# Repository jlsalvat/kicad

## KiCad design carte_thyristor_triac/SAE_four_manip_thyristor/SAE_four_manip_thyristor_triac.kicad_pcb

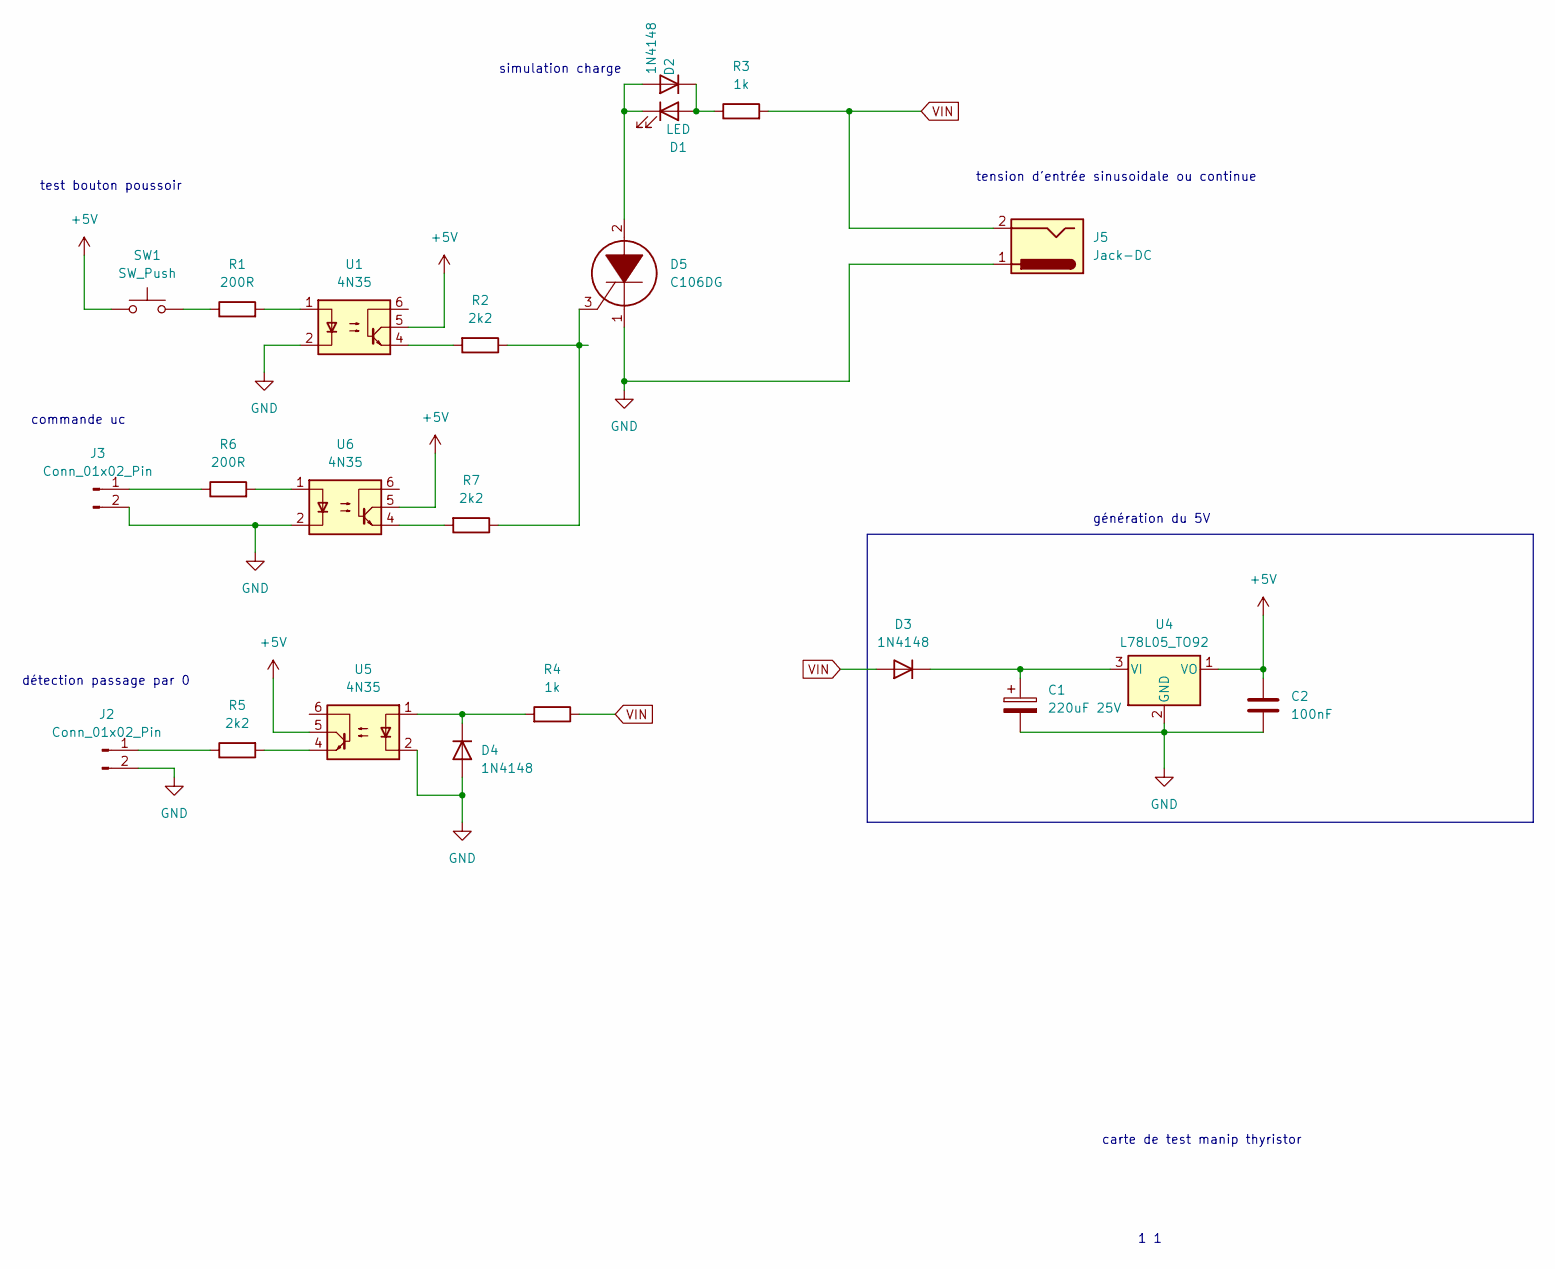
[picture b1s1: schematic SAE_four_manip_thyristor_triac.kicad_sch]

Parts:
C1: 220uF 25V; C_Radial_D6.3mm_H5.0mm_P2.50mm
C2: 100nF; C_Rect_L4.6mm_W3.0mm_P2.50mm_MKS02_FKP02
D1: LED; LED_D3.0mm
D2, D3, D4: 1N4148; D_DO-35_SOD27_P7.62mm_Horizontal
D5: C106DG; Manufacturer_Part_Number C106DG; Mouser Part Number 863-C106DG
J2, J3: Conn_01x02_Pin; PinHeader_1x02_P2.54mm_Vertical
J5: Jack-DC; BarrelJack_GCT_DCJ200-10-A_Horizontal_3D
R1, R6: 200R; R_Axial_DIN0207_L6.3mm_D2.5mm_P10.16mm_Horizontal
R2, R5, R7: 2k2; R_Axial_DIN0207_L6.3mm_D2.5mm_P10.16mm_Horizontal
R3, R4: 1k; R_Axial_DIN0207_L6.3mm_D2.5mm_P10.16mm_Horizontal
SW1: SW_Push; SW_PUSH_6mm
U1, U5, U6: 4N35; DIP-6_W7.62mm
U4: L78L05_TO92; TO-92_Inline

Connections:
+5V: C2.1, SW1.1, U1.5, U4.1 (VO), U5.5, U6.5
GND: C1.2, C2.2, D4.2 (A), D5.1, J2.2, J3.2, J5.1, U1.2, U4.2 (GND), U5.2, U6.2
unnamed: D1.2 (A), D2.1 (K), R3.1
unnamed: D1.1 (K), D2.2 (A), D5.2
unnamed: C1.1, D3.1 (K), U4.3 (VI)
unnamed: D4.1 (K), R4.2, U5.1
unnamed: D5.3, R2.1, R7.1
unnamed: J2.1, R5.1
unnamed: J3.1, R6.1
unnamed: R1.1, SW1.2
unnamed: R1.2, U1.1
unnamed: R2.2, U1.4
unnamed: R5.2, U5.4
unnamed: R6.2, U6.1
unnamed: R7.2, U6.4
VIN: D3.2 (A), J5.2, R3.2, R4.1

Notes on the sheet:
tension d'entrée sinusoidale ou continue
commande uc
détection passage par 0
carte de test manip thyristor
simulation charge
génération du 5V
1 1
test bouton poussoir

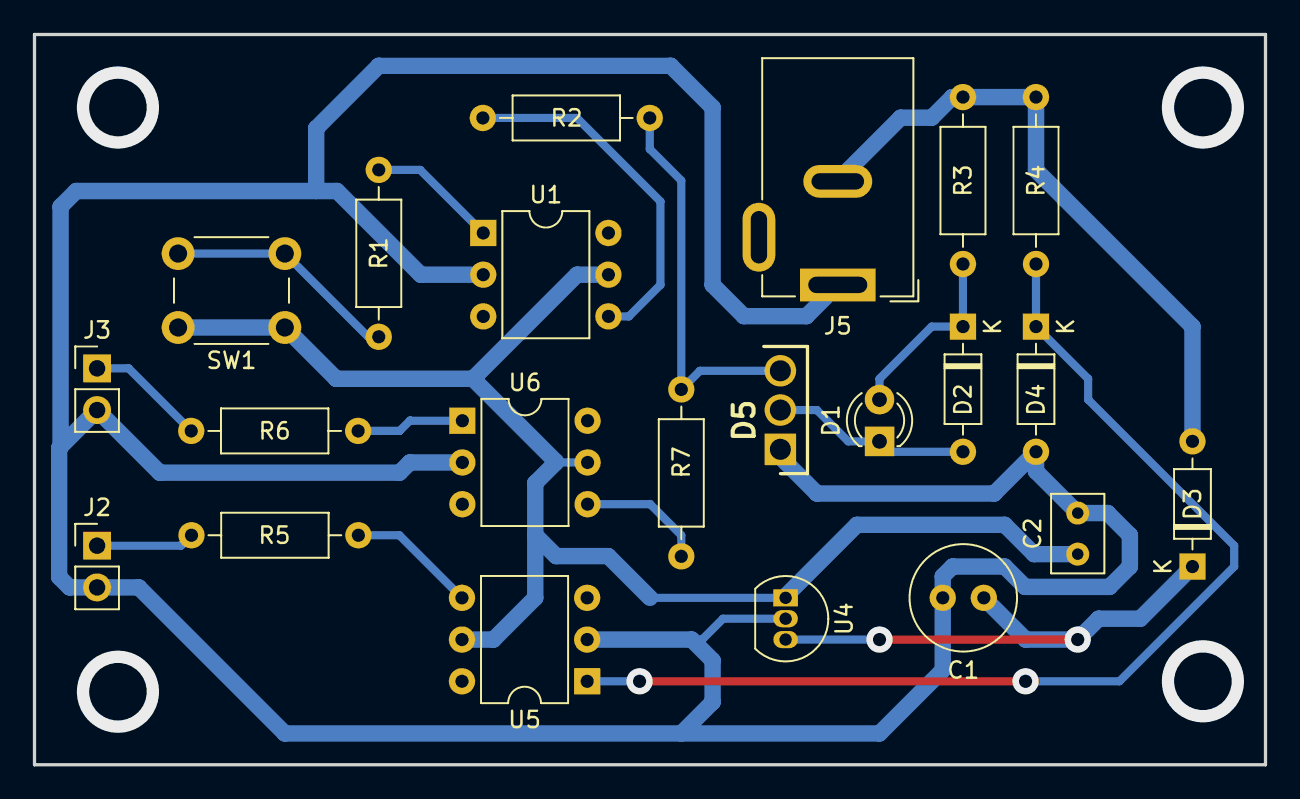
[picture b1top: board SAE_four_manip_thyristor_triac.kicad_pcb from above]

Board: 2 copper layers, 74.9 x 44.4 mm, 22 parts (0 on the bottom side), 16 nets.

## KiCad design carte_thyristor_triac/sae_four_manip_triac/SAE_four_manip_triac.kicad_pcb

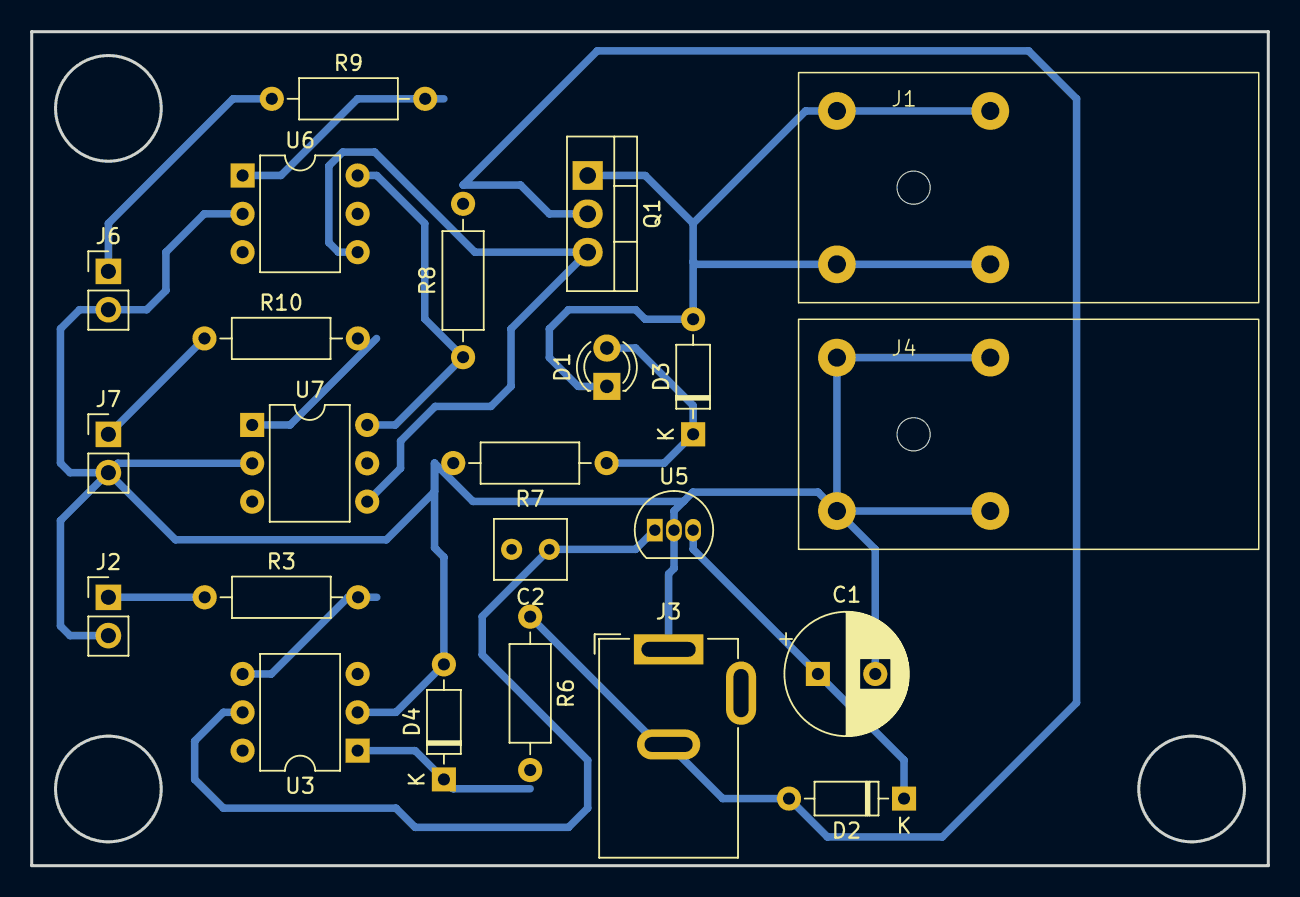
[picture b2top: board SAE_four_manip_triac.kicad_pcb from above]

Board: 2 copper layers, 81.9 x 55.2 mm, 23 parts (0 on the bottom side), 15 nets.

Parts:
C1: 220uF 25V; CP_Radial_D8.0mm_P3.80mm
C2: 100nF; C_Rect_L4.6mm_W3.8mm_P2.50mm_MKS02_FKP02
D1: LED; LED_D3.0mm
D2, D3, D4: 1N4148; D_DO-35_SOD27_P7.62mm_Horizontal
J1: SWEB_8094_Au___SW; douille_4mm_SWEB_8094_rouge
J2, J6, J7: Conn_01x02_Pin; PinHeader_1x02_P2.54mm_Vertical
J3: Jack-DC; BarrelJack_GCT_DCJ200-10-A_Horizontal_3D
J4: SWEB_8094_Au___SW; douille_4mm_SWEB_8094_noire
Q1: BT136-600; TO-220-3_Vertical
R3: 2k2; R_Axial_DIN0207_L6.3mm_D2.5mm_P10.16mm_Horizontal
R6, R7: 1k; R_Axial_DIN0207_L6.3mm_D2.5mm_P10.16mm_Horizontal
R8, R9, R10: 200R; R_Axial_DIN0207_L6.3mm_D2.5mm_P10.16mm_Horizontal
U3: 4N35; DIP-6_W7.62mm
U5: L78L05_TO92; TO-92_Inline
U6: MOC3022M; DIP-6_W7.62mm
U7: MOC3061M; DIP-6_W7.62mm

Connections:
+5V: C2.1, U3.5, U5.1 (VO)
GND: C1.2, C2.2, D4.2 (A), J2.2, J3.1, J4.1, J4.2, J4.3, J4.4, J6.2, J7.2, R7.2, U3.2, U5.2 (GND), U6.2, U7.2
unnamed: D1.2 (A), D3.1 (K), R7.1
unnamed: D1.1 (K), D3.2 (A), J1.1, J1.2, J1.3, J1.4, Q1.1 (A1)
unnamed: C1.1, D2.1 (K), U5.3 (VI)
unnamed: D4.1 (K), R6.2, U3.1
unnamed: J2.1, R3.1
unnamed: J6.1, R9.1
unnamed: J7.1, R10.1
unnamed: Q1.3 (G), U6.4, U7.4
unnamed: R3.2, U3.4
unnamed: R8.1, U6.6, U7.6
unnamed: R9.2, U6.1
unnamed: R10.2, U7.1
VIN: D2.2 (A), J3.2, Q1.2 (A2), R6.1, R8.2

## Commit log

2023-10-23 update triac et librairies
2023-10-23 update thyristor triac et docs
